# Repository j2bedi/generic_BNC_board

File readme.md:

Project files contained within the repo and thus are "git-able"

production files located in releases 

thanks

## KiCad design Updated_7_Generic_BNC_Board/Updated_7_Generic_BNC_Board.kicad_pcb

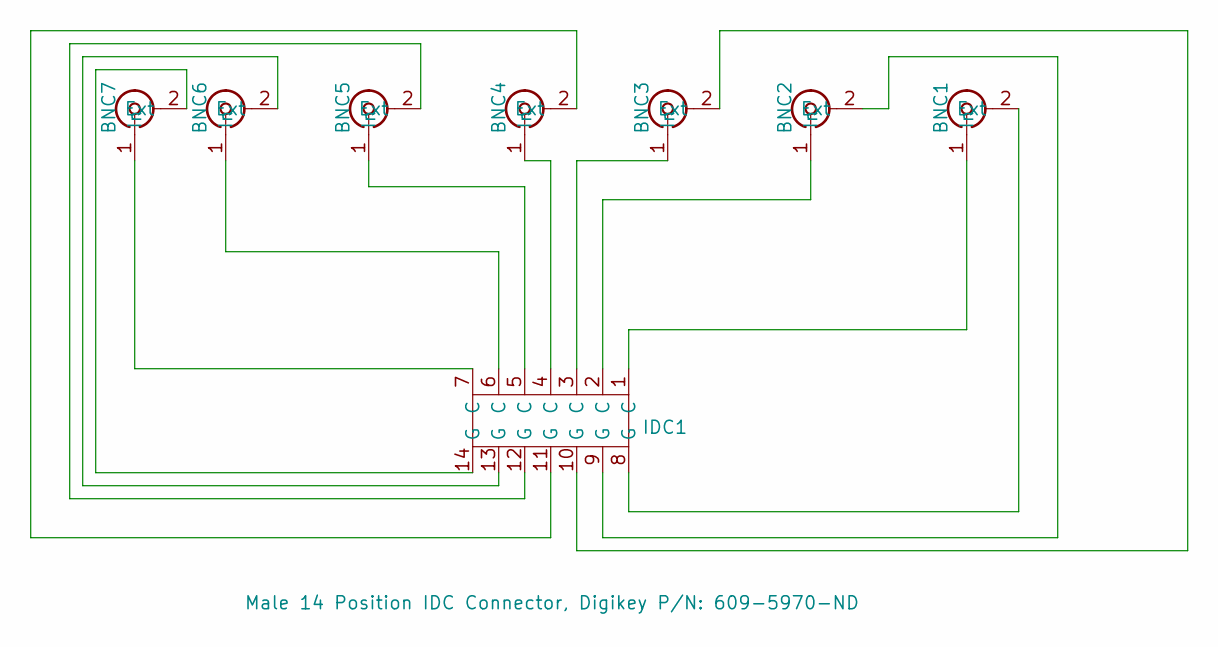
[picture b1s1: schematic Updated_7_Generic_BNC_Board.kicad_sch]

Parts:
BNC1, BNC2, BNC3, BNC4, BNC5, BNC6, BNC7: Coaxial Connectors RA, Digikey P/N: WM5514-ND; BNC new
IDC1: Male 14 Position IDC Connector, Digikey P/N: 609-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; Male IDC Connector

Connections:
unnamed: BNC1.2 (Ext), IDC1.8 (G)
unnamed: BNC1.1 (In), IDC1.1 (C)
unnamed: BNC2.2 (Ext), IDC1.9 (G)
unnamed: BNC2.1 (In), IDC1.2 (C)
unnamed: BNC3.2 (Ext), IDC1.10 (G)
unnamed: BNC3.1 (In), IDC1.3 (C)
unnamed: BNC4.2 (Ext), IDC1.11 (G)
unnamed: BNC4.1 (In), IDC1.4 (C)
unnamed: BNC5.2 (Ext), IDC1.12 (G)
unnamed: BNC5.1 (In), IDC1.5 (C)
unnamed: BNC6.2 (Ext), IDC1.13 (G)
unnamed: BNC6.1 (In), IDC1.6 (C)
unnamed: BNC7.2 (Ext), IDC1.14 (G)
unnamed: BNC7.1 (In), IDC1.7 (C)

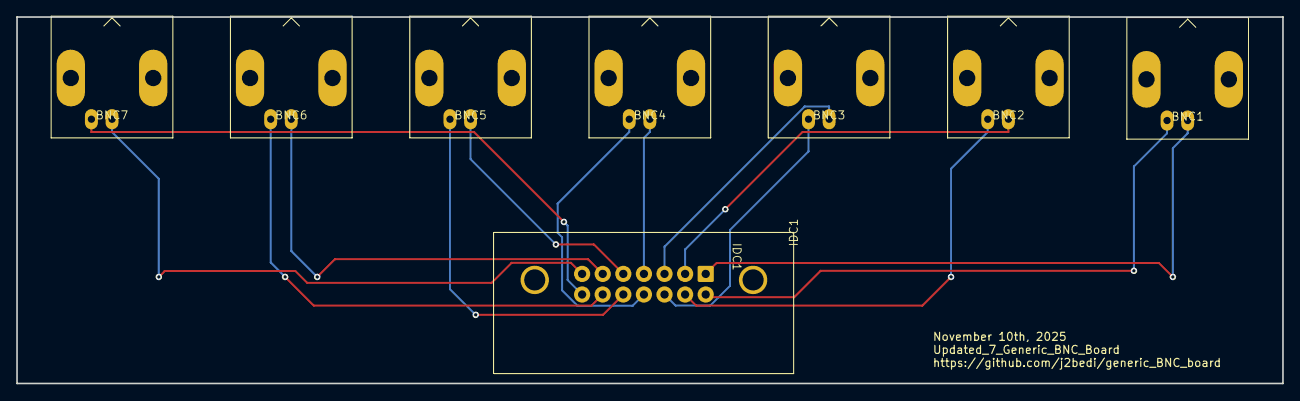
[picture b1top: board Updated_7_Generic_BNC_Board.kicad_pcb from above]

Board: 2 copper layers, 156.1 x 45.2 mm, 8 parts (0 on the bottom side), 14 nets.

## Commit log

2025-10-28 Add project overview to README
    Includes a brief overview of project files and structure.
2025-10-28 Added project files
    Added project files for Generic BNC board with 7 BNC connections
2025-11-19 Updated PCB for the generic bnc board
    Adjusted the foot print of the BNC connector. Previously the 2 signal terminals and 2 supporting studs did not match the BNC connectors in the lab inventory.
